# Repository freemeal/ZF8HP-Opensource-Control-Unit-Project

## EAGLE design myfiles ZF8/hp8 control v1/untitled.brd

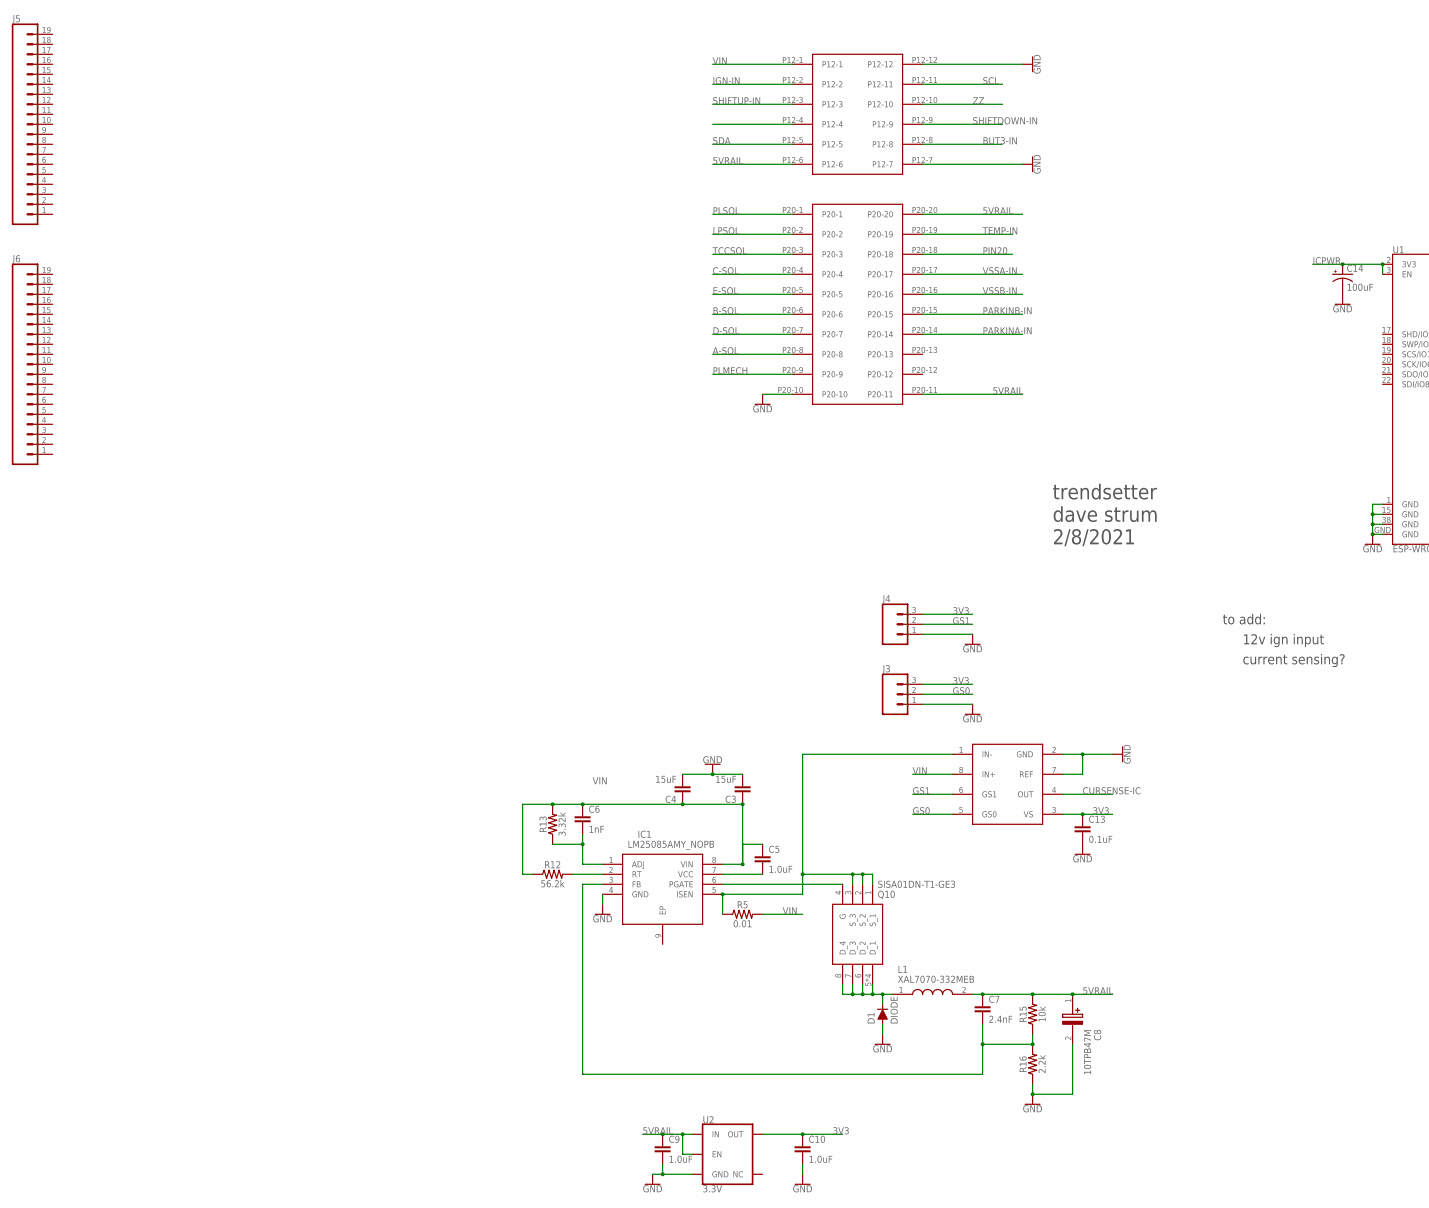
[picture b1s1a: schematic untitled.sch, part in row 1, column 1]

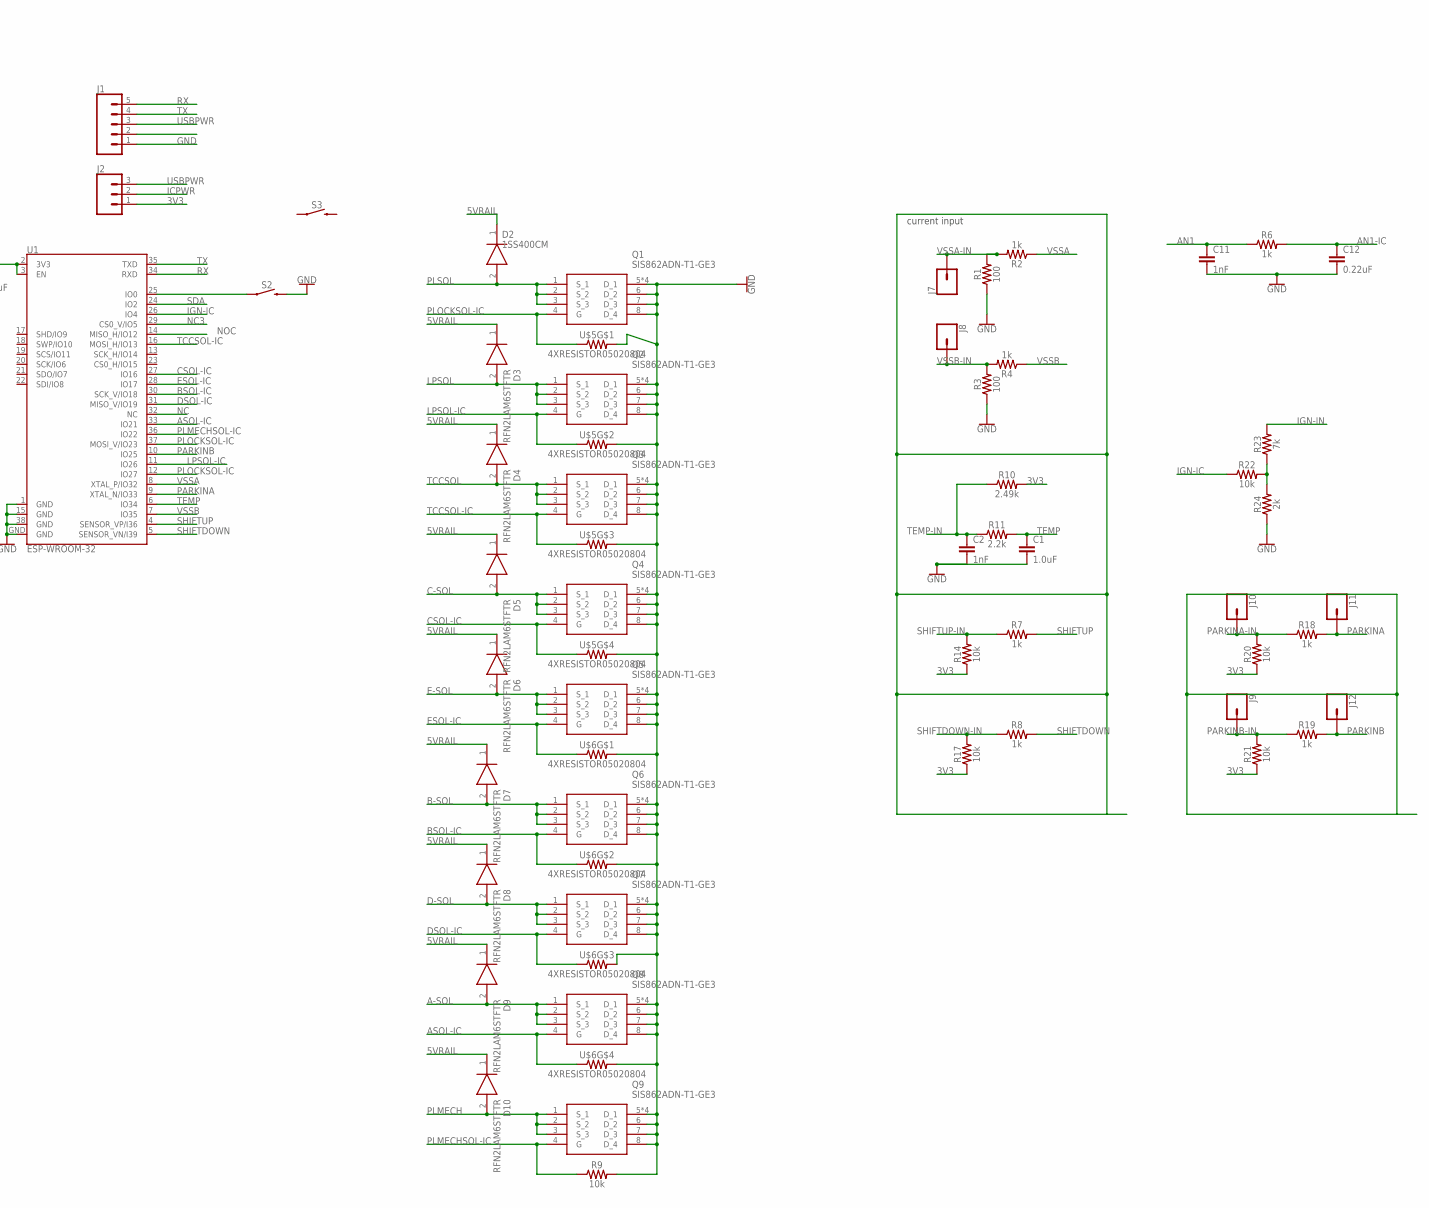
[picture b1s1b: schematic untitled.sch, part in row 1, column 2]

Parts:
C1, C5, C9, C10: 1.0uF; 0603
C2, C6, C11: 1nF; 0603
C3, C4: 15uF; 0805
C7: 2.4nF; 0603
C8: 10TPB47M; CAPPM3528X210N
C12: 0.22uF; 0603
C13: 0.1uF; 0603
C14: 100uF; EIA7343
D1: DIODE; DPAK
D2: 1SS400CM; PMDTM
D3, D4, D5, D6, D7, D8, D9, D10: RFN2LAM6STFTR; PMDTM
IC1: LM25085AMY_NOPB; SOP65P490X109-9N
J1: CONN_05; 1X05
J2, J3, J4: CONN_03LOCK_NO_SILK; 1X03_LOCK_NO_SILK
J5, J6: CONN_191X19_NO_SILK; 1X19_NO_SILK
J7, J8, J9, J10, J11, J12: CONN_01PTH_NO_SILK_KIT; 1X01NS_KIT
L1: XAL7070-332MEB; XAL7070332MEB
Q1, Q2, Q3, Q4, Q5, Q6, Q7, Q8, Q9: SIS862ADN-T1-GE3; SIS862DNT1GE3
Q10: SISA01DN-T1-GE3; SIS862DNT1GE3
R1, R3: 100; 0603
R2, R4, R6, R7, R8, R18, R19: 1k; 0603
R5: 0.01; 2512
R9, R14, R15, R17, R20, R21, R22: 10k; 0603
R10: 2.49k; 0603
R11, R16: 2.2k; 0603
R12: 56.2k; 0603
R13: 3.32k; 0603
R23: 7k; 0603
R24: 2k; 0603
S2, S3: MOMENTARY-SWITCH-SPST-SMD-4.6X2.8MM; TACTILE_SWITCH_SMD_4.6X2.8MM
U1: ESP-WROOM-32
U2: 3.3V; SOT23-5
U$1: MODICEMEMX32
U$4: INA229; MSOP8
U$5, U$6: 4XRESISTOR05020804; 4XRESISTOR0804

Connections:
3V3: C10.1, C13.1, J2.1, J3.3, J4.3, R10.2, R14.1, R17.1, R20.1, R21.1, U2.5 (OUT), U$4.3 (VS)
5VRAIL: C7.1, C8.1 (+), C9.1, D2.1 (K), D3.1 (K), D4.1 (K), D5.1 (K), D6.1 (K), D7.1 (K), D8.1 (K), D9.1 (K), D10.1 (K), L1.2, R15.2, U2.1 (IN), U2.3 (EN), U$1.P12-6, U$1.P20-11, U$1.P20-20
A-SOL: D9.2 (A), Q8.1 (S_1), Q8.2 (S_2), Q8.3 (S_3), U$1.P20-8
AN1: C11.1, R6.1
AN1-IC: C12.1, R6.2
ASOL-IC: Q8.4 (G), U1.33 (IO21), U$6.P$7 (1)
B-SOL: D7.2 (A), Q6.1 (S_1), Q6.2 (S_2), Q6.3 (S_3), U$1.P20-6
BSOL-IC: Q6.4 (G), U1.30 (SCK_V/IO18), U$6.P$3 (1)
BUT3-IN: U$1.P12-8
C-SOL: D5.2 (A), Q4.1 (S_1), Q4.2 (S_2), Q4.3 (S_3), U$1.P20-4
CSOL-IC: Q4.4 (G), U1.27 (IO16), U$5.P$7 (1)
CURSENSE-IC: U$4.4 (OUT)
D-SOL: D8.2 (A), Q7.1 (S_1), Q7.2 (S_2), Q7.3 (S_3), U$1.P20-7
DSOL-IC: Q7.4 (G), U1.31 (MISO_V/IO19), U$6.P$5 (1)
E-SOL: D6.2 (A), Q5.1 (S_1), Q5.2 (S_2), Q5.3 (S_3), U$1.P20-5
ESOL-IC: Q5.4 (G), U1.28 (IO17), U$6.P$1 (1)
GND: C1.2, C2.2, C3.2, C4.2, C8.2 (-), C9.2, C10.2, C11.2, C12.2, C13.2, C14.C (-), D1.1 (A), D1.3 (A), IC1.4 (GND), J1.1, J3.1, J4.1, Q1.5 (D_1), Q1.6 (D_2), Q1.7 (D_3), Q1.8 (D_4), Q1.9 (D_1), Q1.10 (D_1), Q1.11 (D_1), Q2.5 (D_1), Q2.6 (D_2), Q2.7 (D_3), Q2.8 (D_4), Q2.9 (D_1), Q2.10 (D_1), Q2.11 (D_1), Q3.5 (D_1), Q3.6 (D_2), Q3.7 (D_3), Q3.8 (D_4), Q3.9 (D_1), Q3.10 (D_1), Q3.11 (D_1), Q4.5 (D_1), Q4.6 (D_2), Q4.7 (D_3), Q4.8 (D_4), Q4.9 (D_1), Q4.10 (D_1), Q4.11 (D_1), Q5.5 (D_1), Q5.6 (D_2), Q5.7 (D_3), Q5.8 (D_4), Q5.9 (D_1), Q5.10 (D_1), Q5.11 (D_1), Q6.5 (D_1), Q6.6 (D_2), Q6.7 (D_3), Q6.8 (D_4), Q6.9 (D_1), Q6.10 (D_1), Q6.11 (D_1), Q7.5 (D_1), Q7.6 (D_2), Q7.7 (D_3), Q7.8 (D_4), Q7.9 (D_1), Q7.10 (D_1), Q7.11 (D_1), Q8.5 (D_1), Q8.6 (D_2), Q8.7 (D_3), Q8.8 (D_4), Q8.9 (D_1), Q8.10 (D_1), Q8.11 (D_1), Q9.5 (D_1), Q9.6 (D_2), Q9.7 (D_3), Q9.8 (D_4), Q9.9 (D_1), Q9.10 (D_1), Q9.11 (D_1), R1.1, R3.1, R9.2, R16.1, R24.1, S2.3 (2), S2.4 (2), U1.1 (GND), U1.15 (GND), U1.38 (GND), U1.GND, U2.2 (GND), U$1.P12-7, U$1.P12-12, U$1.P20-10, U$4.2 (GND), U$4.7 (REF), U$5.P$2 (2), U$5.P$4 (2), U$5.P$6 (2), U$5.P$8 (2), U$6.P$2 (2), U$6.P$4 (2), U$6.P$6 (2), U$6.P$8 (2)
GS0: J3.2, U$4.5 (GS0)
GS1: J4.2, U$4.6 (GS1)
ICPWR: C14.A (+), J2.2, U1.2 (3V3), U1.3 (EN)
IGN-IC: R22.1, U1.26 (IO4)
IGN-IN: R23.2, U$1.P12-2
LPSOL: D3.2 (A), Q2.1 (S_1), Q2.2 (S_2), Q2.3 (S_3), U$1.P20-2
LPSOL-IC: Q2.4 (G), U1.11 (IO26), U$5.P$3 (1)
unnamed: S2.1, S2.2 (1), U1.25 (IO0)
unnamed: R22.2, R23.1, R24.2
unnamed: IC1.2 (RT), R12.2
unnamed: C5.2, IC1.7 (VCC)
unnamed: C6.2, IC1.1 (ADJ), R13.1
unnamed: IC1.5 (ISEN), Q10.1 (S_1), Q10.2 (S_2), Q10.3 (S_3), R5.P$1 (1), U$4.1 (IN-)
unnamed: IC1.6 (PGATE), Q10.4 (G)
unnamed: D1.4 (C), L1.1, Q10.5 (D_1), Q10.6 (D_2), Q10.7 (D_3), Q10.8 (D_4), Q10.9 (D_1), Q10.10 (D_1), Q10.11 (D_1)
unnamed: C7.2, IC1.3 (FB), R15.1, R16.2
NC: U1.32 (NC)
NC3: U1.29 (CS0_V/IO5)
NOC: U1.14 (MISO_H/IO12)
PARKINA: J11.1, R18.2, U1.9 (XTAL_N/IO33)
PARKINA-IN: J10.1, R18.1, R20.2, U$1.P20-14
PARKINB: J12.1, R19.2, U1.10 (IO25)
PARKINB-IN: J9.1, R19.1, R21.2, U$1.P20-15
PIN20: U$1.P20-18
PLMECH: D10.2 (A), Q9.1 (S_1), Q9.2 (S_2), Q9.3 (S_3), U$1.P20-9
PLMECHSOL-IC: Q9.4 (G), R9.1, U1.36 (IO22)
PLOCKSOL-IC: Q1.4 (G), U1.12 (IO27), U1.37 (MOSI_V/IO23), U$5.P$1 (1)
PLSOL: D2.2 (A), Q1.1 (S_1), Q1.2 (S_2), Q1.3 (S_3), U$1.P20-1
RX: J1.5, U1.34 (RXD)
SCL: U$1.P12-11
SDA: U1.24 (IO2), U$1.P12-5
SHIFTDOWN: R8.2, U1.5 (SENSOR_VN/I39)
SHIFTDOWN-IN: R8.1, R17.2, U$1.P12-9
SHIFTUP: R7.2, U1.4 (SENSOR_VP/I36)
SHIFTUP-IN: R7.1, R14.2, U$1.P12-3
TCCSOL: D4.2 (A), Q3.1 (S_1), Q3.2 (S_2), Q3.3 (S_3), U$1.P20-3
TCCSOL-IC: Q3.4 (G), U1.16 (MOSI_H/IO13), U$5.P$5 (1)
TEMP: C1.1, R11.2, U1.6 (IO34)
TEMP-IN: C2.1, R10.1, R11.1, U$1.P20-19
TX: J1.4, U1.35 (TXD)
USBPWR: J1.3, J2.3
VIN: C3.1, C4.1, C5.1, C6.1, IC1.8 (VIN), R5.P$2 (2), R12.1, R13.2, U$1.P12-1, U$4.8 (IN+)
VSSA: R2.1, U1.8 (XTAL_P/IO32)
VSSA-IN: J7.1, R1.2, R2.2, U$1.P20-17
VSSB: R4.1, U1.7 (IO35)
VSSB-IN: J8.1, R3.2, R4.2, U$1.P20-16
ZZ: U$1.P12-10

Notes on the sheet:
current input
to add:
12v ign input
current sensing?
trendsetter dave strum 2/8/2021

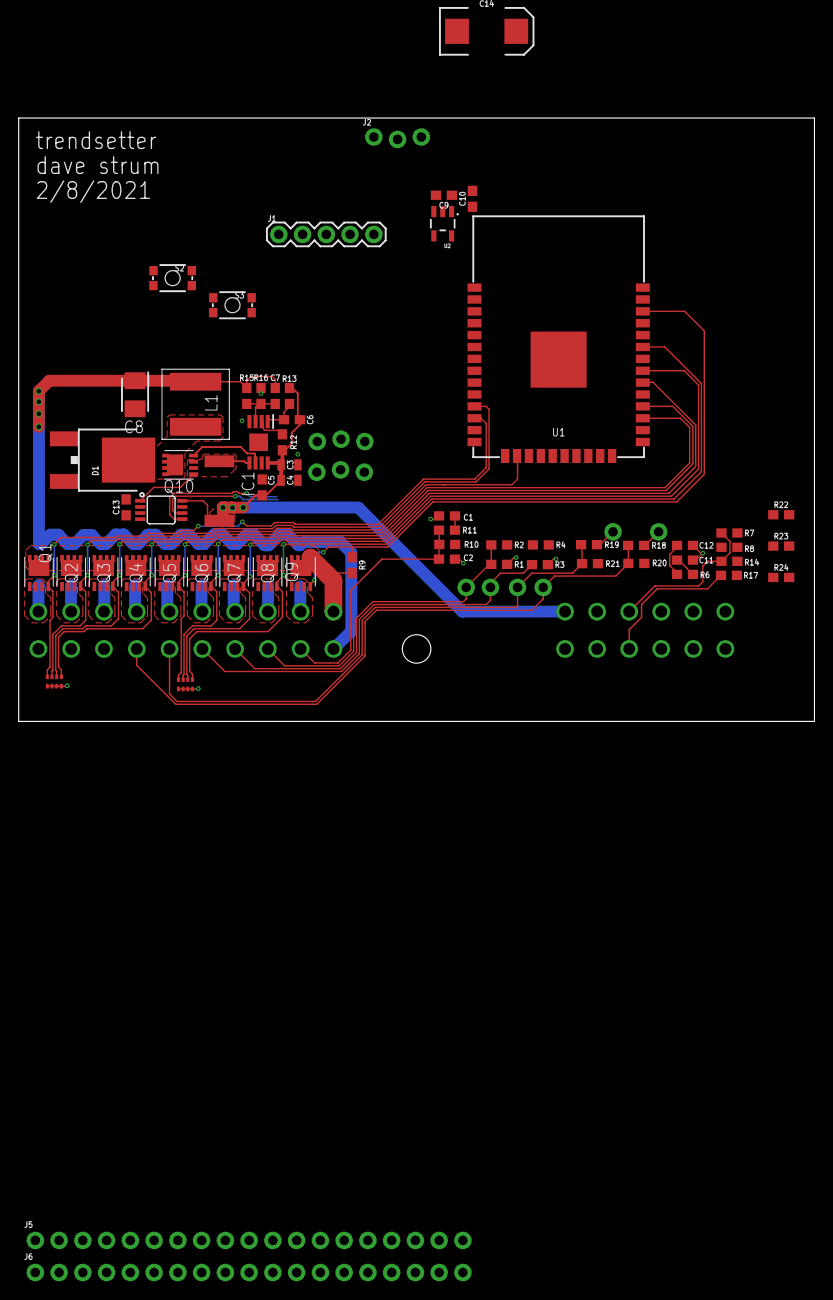
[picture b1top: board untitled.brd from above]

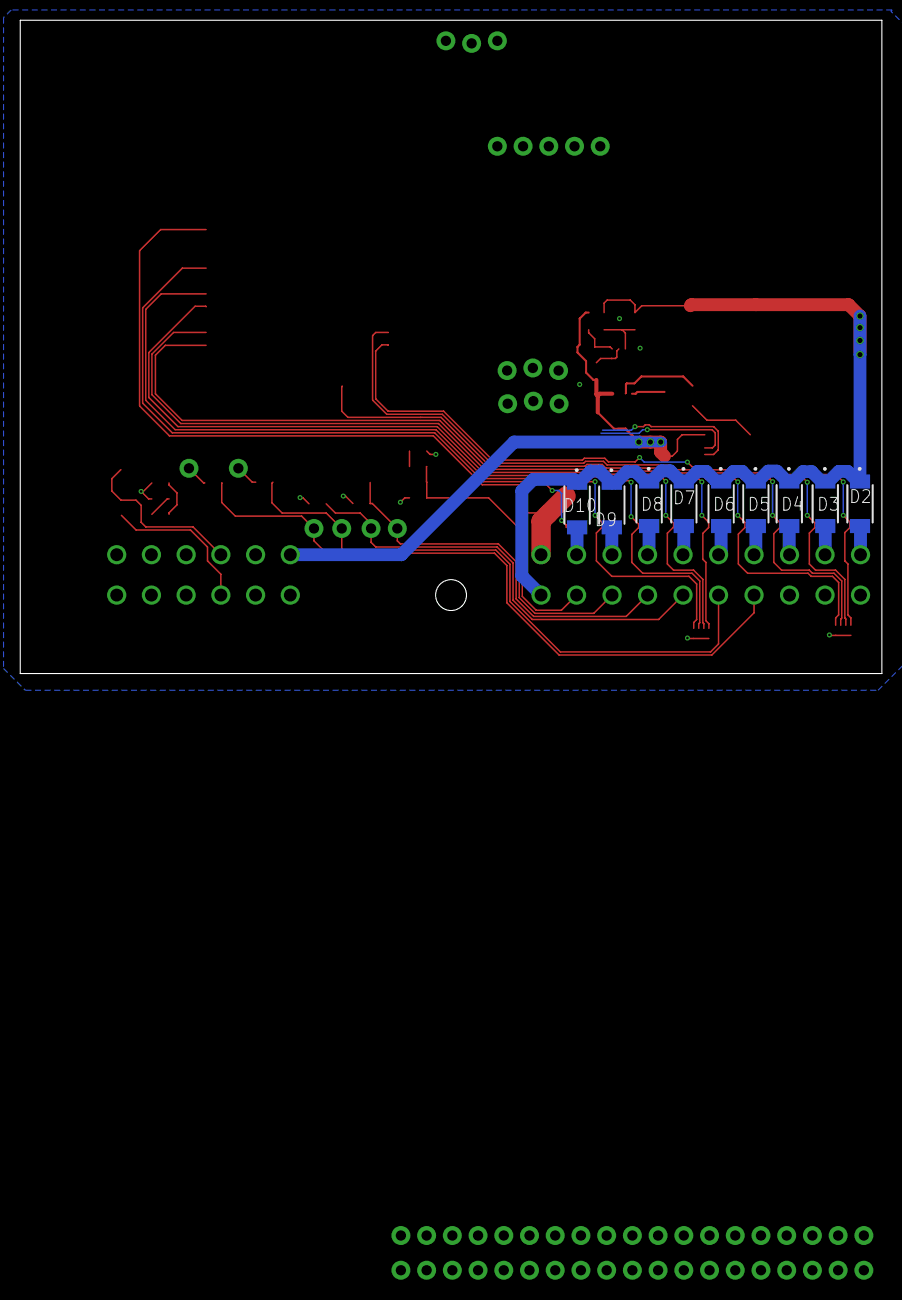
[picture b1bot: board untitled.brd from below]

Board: 2 copper layers, 85.1 x 64.5 mm, 80 parts (9 on the bottom side), 56 nets.

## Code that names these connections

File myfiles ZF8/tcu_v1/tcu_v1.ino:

//
//  ZF8HP TCU 
//		trendsetter
//  	dave strum
//		2/8/2021
//
//  for esp32 board
//
// target mac ESP Board MAC Address:  24:6F:28:88:03:24

#include <esp_now.h>
#include "WiFi.h"


// ----- commands
#define		SHIFTDOWN_COM	1
#define		SHIFTUP_COM		2
#define		REVERSE_COM		3
#define		POWEROFF_COM	4
#define		WAKE_COM		5
// -----------------
// ----- States
#define		BOOT			0
#define		PARK			1
#define		FORWARD			2
#define		REVERSE			3
#define		SLEEP			4
// ------------------


uint8_t broadcastAddress[] = {0x24, 0x6F, 0x28, 0x88, 0x03, 0x24};

#define		ASOL		23
#define		BSOL		22
#define		CSOL		21
#define		DSOL		19
#define		ESOL		18

#define		TCCSOL		24
#define		LPSOL		25
#define		PLSOL		26
#define		PARKLOCK	27

#define		VSSA		1
#define		VSSB		1

#define		PARKA		1
#define		PARKB		1

#define		SOLFREQ 	64
#define		SOLRES		8

#define		LPSCHAN		1
#define		TCCCHAN		2
#define		PLCHAN		3
#define		BSOLCHAN	4


// ------ main program stuff ----
#define DELAYSLOW	100  // 10hz
#define DELAYFAST	10		// 100hz

#define SERIAL_EN                //comment out if you don't want any debug output

#ifdef SERIAL_EN
  #define DEBUG(input)   {Serial.print(input); delay(1);}
  #define DEBUGln(input) {Serial.println(input); delay(1);}
#else
  #define DEBUG(input);
  #define DEBUGln(input);
#endif

int recvFlag = 0;
int curGear = 1;  // 0=in park/pawl applied
int lastGear = 0;
int nextGear = 0;
int curTemp = 0;
int curVSS = 0;


String success;
//Structure example to send data
//Must match the receiver structure
typedef struct struct_message {
	uint16_t seq;
    int temp;
    int gear;
    int vss;
	int vssb;
	int command;
} struct_message;

uint16_t seq;
uint16_t lastPacks[8];
int packIndex=0;

// Create a struct_message called BME280Readings to hold sensor readings
struct_message TCUcommand;
// Create a struct_message to hold incoming sensor readings
struct_message incomingReadings;

// Callback when data is sent
void OnDataSent(const uint8_t *mac_addr, esp_now_send_status_t status) {
  //Serial.print("\r\nLast Packet Send Status:\t");
  Serial.println(status == ESP_NOW_SEND_SUCCESS ? "Delivery Success" : "Delivery Fail");
  DEBUGln("");
}

// Callback when data is received
void OnDataRecv(const uint8_t * mac, const uint8_t *incomingData, int len) {
	memcpy(&incomingReadings, incomingData, sizeof(incomingReadings));
	recvFlag = 1;  // data receive flag
	//Serial.println("rec");
	//Serial.println(incomingReadings.command);
}

void processPacket() {
	if (recvFlag == 0) return;
	recvFlag = 0;
	DEBUG("received:");
	DEBUGln(incomingReadings.seq);
	DEBUG("com:");
	DEBUGln(incomingReadings.command);
	for (int i=0;i<8;i++) {
		if (incomingReadings.seq == lastPacks[i]) { return; } // see if we received this packet id in the last 8 packets
	}
	DEBUGln(" passed seq test");
	seq = incomingReadings.seq;
	if (packIndex++ > 7) packIndex = 0;		// sorta like a circular buffer?
	lastPacks[packIndex] = incomingReadings.seq;
	switch (incomingReadings.command) {
		case REVERSE_COM:		// go to reverse
			
			break;
			
		case SHIFTUP_COM:		// upshift
			if (curGear > 7) break; // already in 8th gear
			if (curGear < 1) break; //	in park
			switch (curGear) {
				case 1:
					shift12();
					break;
				case 2:
					shift23();
					break;
				case 3:
					shift34();
					break;
				case 4:
					shift45();
					break;
				case 5:
					shift56();
					break;
				case 6:
					shift67();
					break;
				case 7:
					shift78();
					break;
				default:
					break;
			}					
			break;
			
		case SHIFTDOWN_COM:		// down shift
			if (curGear < 1) break;	// in park
			if (curGear > 8) break; // in reverse
			switch (curGear) {
				case 2:
					shift21();
					break;
				case 3:
					shift32();
					break;
				case 4:
					shift43();
					break;
				case 5:
					shift54();
					break;
				case 6:
					shift65();
					break;
				case 7:
					shift76();
					break;
				case 8:
					shift87();
					break;
				default:
					break;	
			}
			break;
			
		default:
			break;
	}
	TCUcommand.seq = seq++;TCUcommand.seq = seq++;
	TCUcommand.gear = curGear;
	TCUcommand.temp = curTemp;
	TCUcommand.vss = curVSS;
	sendMsg();	
	DEBUG("gear:");
	DEBUGln(TCUcommand.gear);
}

void sendMsg() {
   // Send message via ESP-NOW
  	for (int i=0;i<2;i++) {   // try sending 3 times
		Serial.print("sending:");
		Serial.print(TCUcommand.seq);
		Serial.print(" try:");
		Serial.println(i);
		esp_err_t result = esp_now_send(broadcastAddress, (uint8_t *) &TCUcommand, sizeof(TCUcommand));
		if (result == ESP_OK) { break; }
	}
}

uint32_t now = 0, prevMillisSlow=0, prevMillisFast=0;

void setup() {
	Serial.begin(115200);
	Serial.println("tcu begin");
	
	pinMode(ASOL, OUTPUT);
	
	ledcSetup(BSOLCHAN, SOLFREQ, SOLRES);
	ledcAttachPin(BSOL, BSOLCHAN);
	
	pinMode(CSOL, OUTPUT);
	pinMode(DSOL, OUTPUT);
	pinMode(ESOL, OUTPUT);
	
	ledcSetup(TCCCHAN, SOLFREQ, SOLRES);
	ledcAttachPin(TCCSOL, TCCCHAN);
	
	ledcSetup(LPSCHAN, SOLFREQ, SOLRES);
	ledcAttachPin(LPSOL, LPSCHAN);
	
	pinMode(PLSOL, OUTPUT);
	pinMode(PARKLOCK, OUTPUT);
	
	pinMode(PARKA, INPUT);
	pinMode(PARKB, INPUT);
	pinMode(VSSA, INPUT);
	pinMode(VSSB, INPUT);
	
	  // Set device as a Wi-Fi Station
  WiFi.mode(WIFI_STA);

  // Init ESP-NOW
  if (esp_now_init() != ESP_OK) {
    Serial.println("Error init ESP-NOW");
    return;
  }
  
  // Once ESPNow is successfully Init, we will register for Send CB to
  // get the status of Trasnmitted packet
  esp_now_register_send_cb(OnDataSent);
  
  // Register peer
  esp_now_peer_info_t peerInfo;
  memcpy(peerInfo.peer_addr, broadcastAddress, 6);
  peerInfo.channel = 0;  
  peerInfo.encrypt = false;
  
  // Add peer        
  if (esp_now_add_peer(&peerInfo) != ESP_OK){
    Serial.println("Failed to add peer");
    return;
  }
  // Register for a callback function that will be called when data is received
  esp_now_register_recv_cb(OnDataRecv);
  
	
	// add safety here:
	// check if we are moving in case we get a reboot while driving
	// read speed or we can also read the park position sensor
	
	//set solenoids for park
	digitalWrite(ASOL, HIGH);
	ledcWrite(BSOLCHAN, 0);
	digitalWrite(CSOL, HIGH);
	digitalWrite(DSOL, HIGH);
	digitalWrite(ESOL, HIGH);
	//ledcWrite(TCCCHAN, 0);
	//ledcWrite(LPSCHAN, 0);
	//digitalWrite(PLSOL, LOW);
	//digitalWrite(PARKLOCK, LOW);

}


void loop() {
	processPacket();
	
	if (millis() - prevMillisSlow >= 10000) {  // 10 hz loop
		Serial.println("sending periodic update");
		DEBUG("gear: ");
		DEBUGln(TCUcommand.gear);
		TCUcommand.seq = seq++;
		TCUcommand.gear = curGear;
		TCUcommand.temp = curTemp++;
		TCUcommand.vss = curVSS++;
		DEBUG("gear: ");
		DEBUGln(TCUcommand.gear);
		sendMsg();
		
		prevMillisSlow = millis();
	}
	
}


void shiftp1() {
	// park to drive (1st gear)
	digitalWrite(PLSOL, HIGH);	// release park pawl
	// check that pawl released (or time delay?)
	ledcWrite(BSOLCHAN, 0); // release B
	digitalWrite(CSOL,LOW);  // apply C
}

void shift12() {
	digitalWrite(CSOL, HIGH); // release C
	delay(50);
	digitalWrite(ESOL, LOW); // apply E
	curGear = 2;
}

void shift23() {
	digitalWrite(ASOL, LOW);  // release A
	digitalWrite(CSOL, LOW);  // apply C
	curGear = 3;
}

void shift34() {
	digitalWrite(CSOL, HIGH);  // release C
	delay(50);
	digitalWrite(DSOL, LOW);  // apply D
	curGear = 4;
}

void shift45() {
	digitalWrite(CSOL, LOW);  // apply C
	delay(50);
	digitalWrite(ESOL, HIGH); // release E
	curGear = 5;
}

void shift56() {
	digitalWrite(BSOL, LOW);  // release B
	digitalWrite(ESOL, LOW);  // Apply E
	curGear = 6;
}

void shift67() {
	digitalWrite(ASOL, HIGH);	// apply A
	digitalWrite(ESOL, HIGH);	// release E
	curGear = 7;
}

void shift78() {
	digitalWrite(CSOL, HIGH);	// release C
	digitalWrite(ESOL, LOW);	//	apply E	
	curGear = 8;
}


void shift21() {
	digitalWrite(CSOL, LOW); // apply C
	delay(50);
	digitalWrite(ESOL, HIGH); // release E
	curGear = 1;
}

void shift32() {
	digitalWrite(ASOL, HIGH);  // apply A
	digitalWrite(CSOL, HIGH);  // release C
	curGear = 2;
}

void shift43() {
	digitalWrite(CSOL, LOW);  // apply C
	delay(50);
	digitalWrite(DSOL, HIGH);  // release D
	curGear = 3;
}

void shift54() {
	digitalWrite(CSOL, HIGH);  // release C
	delay(50);
	digitalWrite(ESOL, LOW); // apply E
	curGear = 4;
}

void shift65() {
	digitalWrite(BSOL, HIGH);  // apply B
	digitalWrite(ESOL, HIGH);  // release E
	curGear = 5;
}

void shift76() {
	digitalWrite(ASOL, LOW);	// release A
	digitalWrite(ESOL, LOW);	// apply E
	curGear = 6;
}

void shift87() {
	digitalWrite(CSOL, LOW);	// apply C
	digitalWrite(ESOL, HIGH);	//	release E	
	curGear = 7;
}

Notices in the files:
parts and their libraries:
SparkFun-Capacitors: Licensing: Creative Commons ShareAlike 4.0 International - https://creativecommons.org/licenses/by-sa/4.0
